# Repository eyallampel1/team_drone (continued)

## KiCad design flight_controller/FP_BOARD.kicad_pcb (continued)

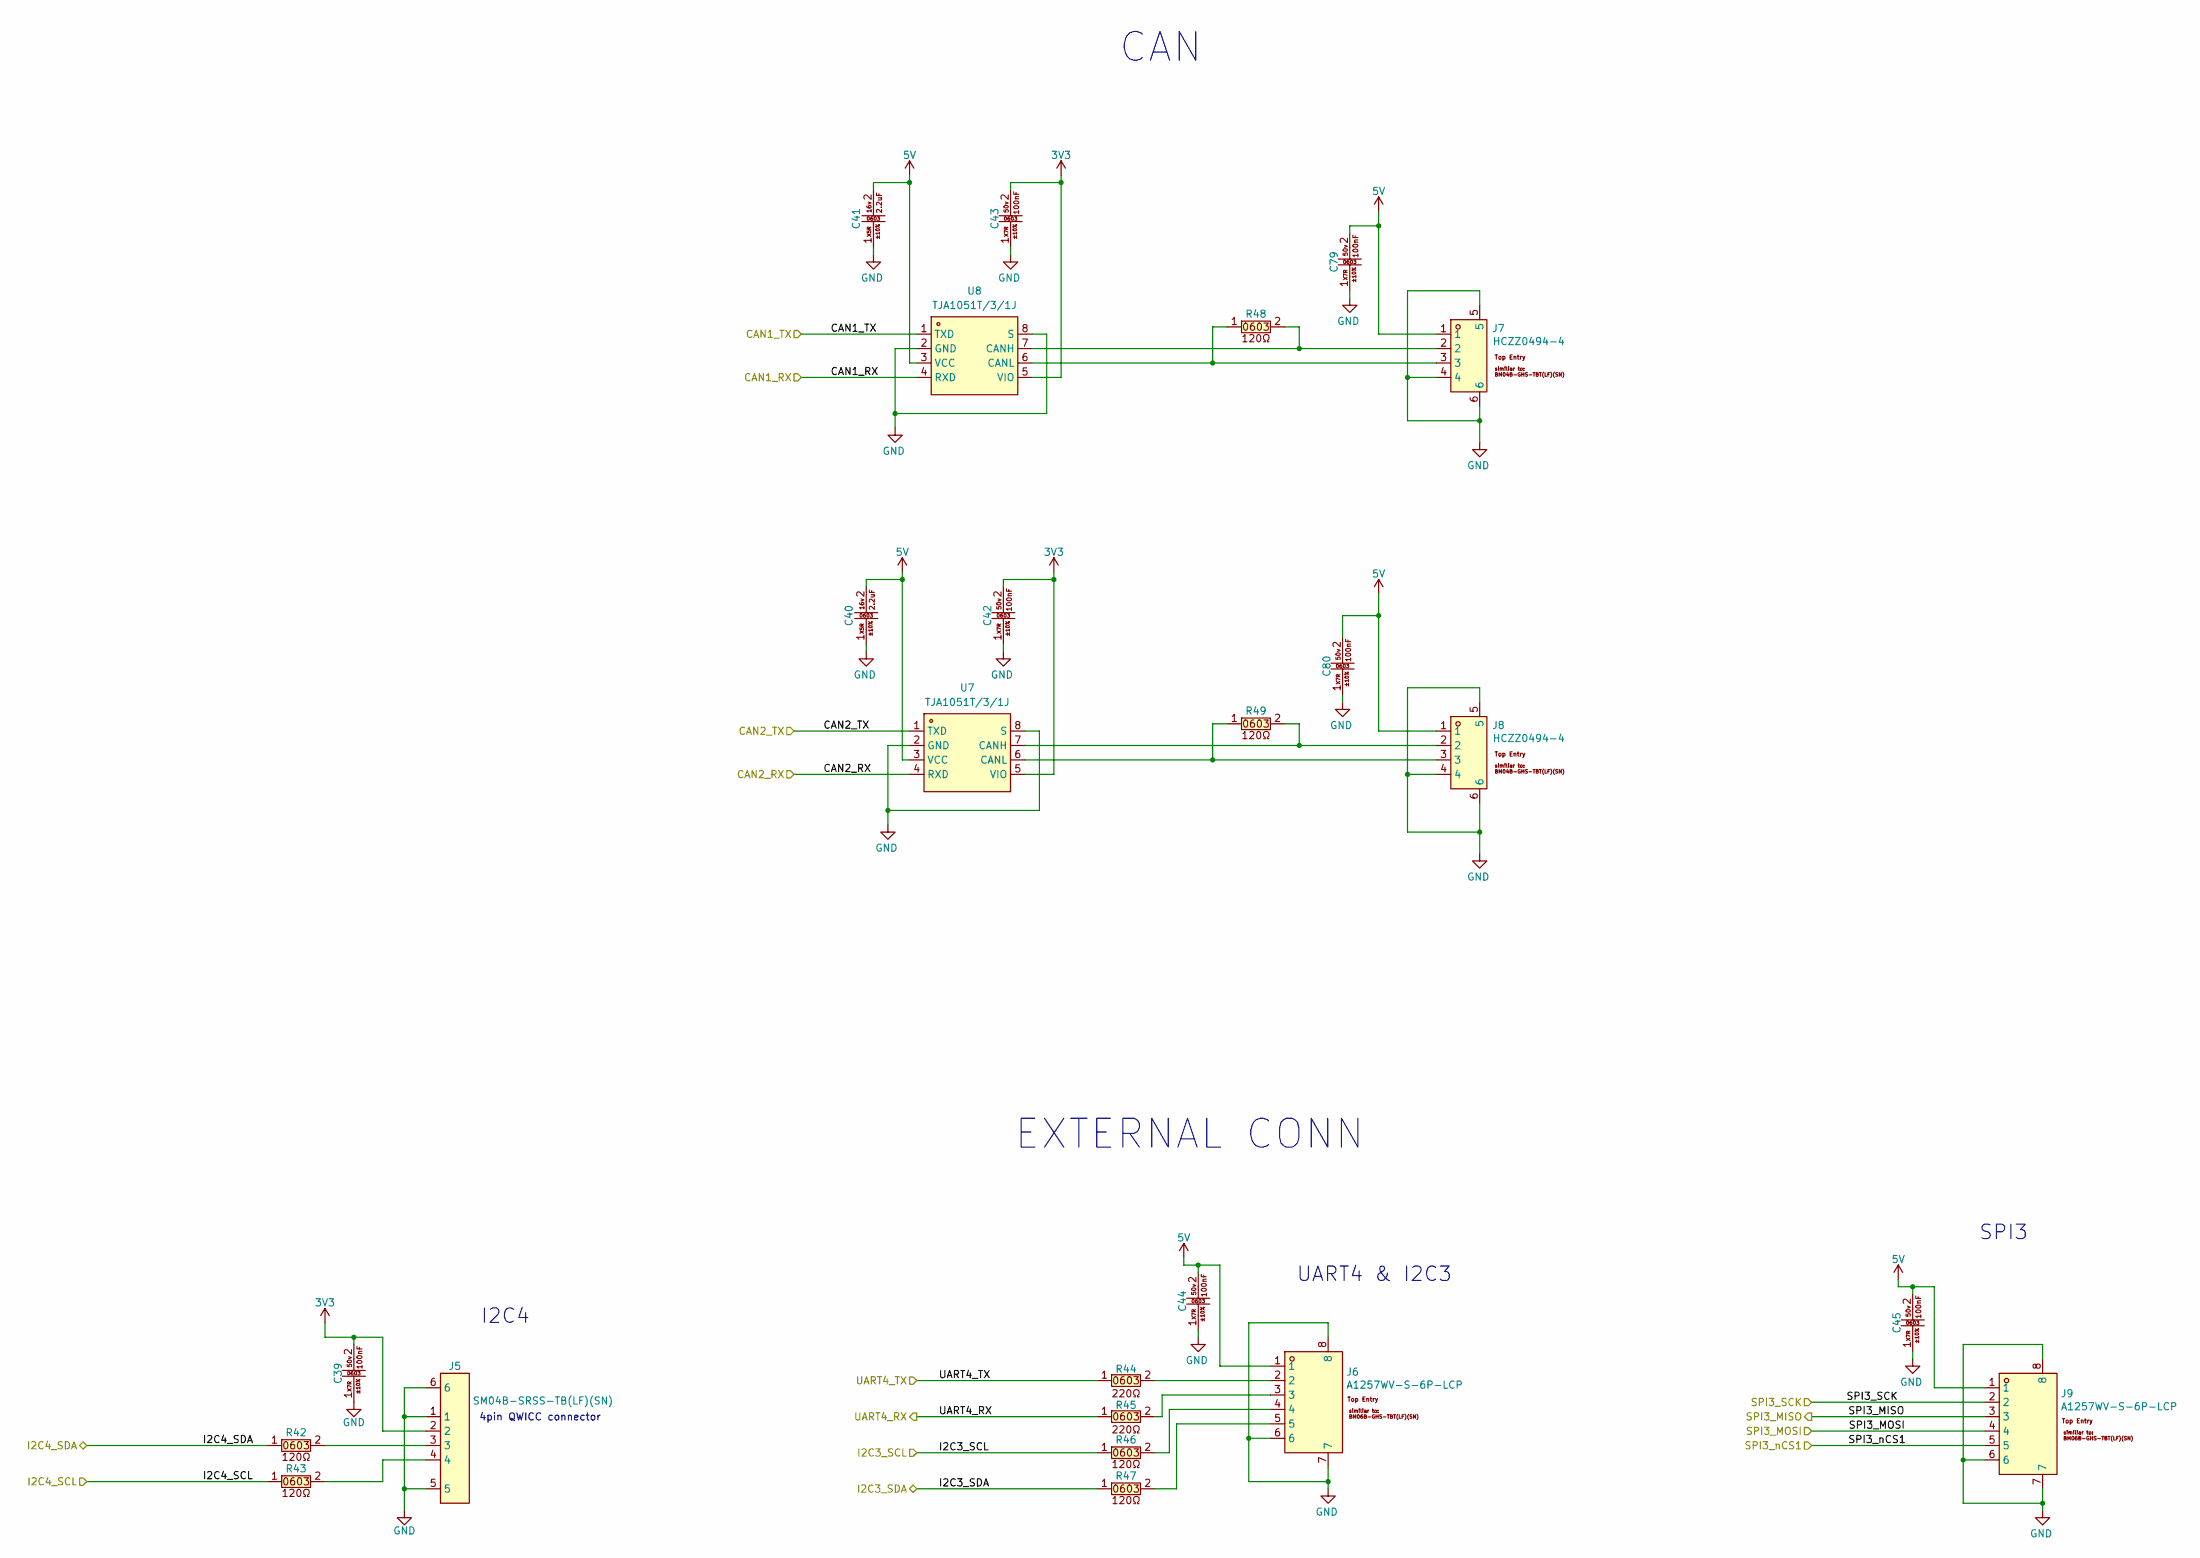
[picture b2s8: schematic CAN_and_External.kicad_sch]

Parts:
C39, C42, C43, C44, C45, C79, C80: CC0603KRX7R9BB104 (100nf , 0603 ,50v ,X7R); C0603; LCSC Part C14663
C40, C41: CL10A225KO8NNNC (2.2uf , 0603,16v,X5R); C0603; LCSC Part C23630
J5: SM04B-SRSS-TB(LF)(SN); CONN-SMD_4P-P1.00_SM04B-SRSS-TB-LF-SN; LCSC Part C160404
J6, J9: A1257WV-S-6P-LCP; CONN-SMD_A1257WV-S-6P; LCSC Part C225122
J7, J8: HCZZ0494-4; CONN-SMD_4P-P1.25_BM04B-GHS-TBT-LF-SN; LCSC Part C7433500
R42, R43, R46, R47, R48, R49: 603WAF1200T5E; R0603; LCSC Part C22787
R44, R45: 0603WAF2200T5E (220ohm , 0603); R0603; LCSC Part C22962
U7, U8: TJA1051T/3/1J; SOIC-8_L4.9-W3.9-P1.27-LS6.0-BL; LCSC Part C38695

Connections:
/FDCAN1_RX: U8.4 (RXD); also elsewhere on the board
/FDCAN1_TX: U8.1 (TXD); also elsewhere on the board
/FDCAN2_RX: U7.4 (RXD); also elsewhere on the board
/FDCAN2_TX: U7.1 (TXD); also elsewhere on the board
/I2C3_SCL: R46.1; also elsewhere on the board
/I2C3_SDA: R47.1; also elsewhere on the board
/I2C4_SCL: R43.1; also elsewhere on the board
/I2C4_SDA: R42.1; also elsewhere on the board
/SPI3_MISO: J9.3; also elsewhere on the board
/SPI3_MOSI: J9.4; also elsewhere on the board
/SPI3_SCK: J9.2; also elsewhere on the board
/SPI3_nCS1: J9.5; also elsewhere on the board
/UART4_RX: R45.1; also elsewhere on the board
/UART4_TX: R44.1; also elsewhere on the board
unnamed: J5.3, R42.2
unnamed: J5.4, R43.2
unnamed: J6.2, R44.2
unnamed: J6.3, R45.2
unnamed: J6.4, R46.2
unnamed: J6.5, R47.2
unnamed: J8.2, R49.2, U7.7 (CANH)
unnamed: J8.3, R49.1, U7.6 (CANL)
unnamed: J7.2, R48.2, U8.7 (CANH)
unnamed: J7.3, R48.1, U8.6 (CANL)

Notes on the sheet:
CAN
UART4 & I2C3
SPI3
4pin QWICC connector
EXTERNAL CONN
I2C4

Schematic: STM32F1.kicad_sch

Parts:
C29, C30: CC0603JRNPO9BN100 (10pF , 0603 ,50V ,X7R); C0603; LCSC Part C106245
C31, C32, C33, C34, C35: CC0603KRX7R9BB104 (100nf , 0603 ,50v ,X7R); C0603; LCSC Part C14663
C36: CL10B105KA8NNNC (1uf ,0603 ,25v ,X7R); C0603; LCSC Part C29936
D3: 0603 Green 509-620mcd; LED0603-RD; LCSC Part C12624
D4: KT-0603R; LED0603-RD; LCSC Part C2286
J21: HB-PH9-12727PB2GOB; HDR-SMD_14P-P1.27-V-M-R2-C7-LS5.5; LCSC Part C6332251
R19, R23, R24: 603WAF1000T5E (100ohm , 0603); R0603; LCSC Part C22775
R20, R21: 0603WAF2200T5E (220ohm , 0603); R0603; LCSC Part C22962
R22, R25: 0603WAF1002T5E (10kohm , 0603); R0603; LCSC Part C25804
SW2: 6.0*6.0*6.0; SW-SMD_4P-L6.0-W6.0-P4.50-LS8.6; LCSC Part C5127964
TP13, TP14, TP15, TP16, TP17: TestPoint; TestPoint_Pad_2.0x2.0mm
U4: STM32F103C8T6; LQFP-48_L7.0-W7.0-P0.50-LS9.0-BL; LCSC Part C8734
X3: X322524MLB4SI_C5210646; CRYSTAL-SMD_4P-L3.2-W2.5-BL; LCSC Part C5210646

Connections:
/IO_CH1: U4.10 (PA0-WKUP); also elsewhere on the board
/IO_CH2: U4.11 (PA1); also elsewhere on the board
/IO_CH3: U4.45 (PB8); also elsewhere on the board
/IO_CH4: U4.46 (PB9); also elsewhere on the board
/IO_CH5: U4.16 (PA6); also elsewhere on the board
/IO_NSAFETY_SWITCH_LED_OUT: U4.26 (PB13); also elsewhere on the board
/IO_PPM_INPUT: U4.29 (PA8); also elsewhere on the board
/IO_RSSI_IN: U4.15 (PA5), U4.33 (PA12); also elsewhere on the board
/IO_SAFETY_SWITCH_IN: U4.41 (PB5); also elsewhere on the board
/IO_SBUS_INPUT: U4.22 (PB11); also elsewhere on the board
/IO_SBUS_OUTPUT: U4.21 (PB10); also elsewhere on the board
/IO_USART1_RX_DSM: J21.13, U4.31 (PA10); also elsewhere on the board
/NSBUS_OUT_EN: U4.40 (PB4); also elsewhere on the board
/STM32F1/FMU_USART6_RX_IO_USART2_TX: R20.2, U4.12 (PA2)
/STM32F1/FMU_USART6_TX_IO_USART2_RX: R21.2, U4.13 (PA3)
/STM32F1/IO_CH6: U4.17 (PA7)
/STM32F1/IO_CH7: U4.18 (PB0)
/STM32F1/IO_CH8: U4.19 (PB1)
/STM32F1/IO_LED1: R23.2, U4.28 (PB15)
/STM32F1/IO_LED2: R24.2, U4.27 (PB14)
/STM32F1/IO_SPARE_GPIO1: TP17.1, U4.42 (PB6)
/STM32F1/IO_SPARE_GPIO2: TP16.1, U4.43 (PB7)
/STM32F1/IO_SWCLK: J21.6, U4.37 (PA14)
/STM32F1/IO_SWDIO: J21.4, U4.34 (PA13)
/STM32F1/IO_SWO: J21.8, U4.39 (PB3)
/STM32F1/IO_USART1_TX_VCP: J21.14, U4.30 (PA9)
/STM32F1/IO_VDD_SERVO_SENS: U4.14 (PA4)
/STM32F1/STM32F1_NRST: SW2.1, SW2.2, U4.7 (NRST)
/STM32F1/USART6_RX_FROM_IO-RC_INPUT: R20.1; also elsewhere on the board
/STM32F1/USART6_TX_TO_IO-NC: R21.1; also elsewhere on the board
unnamed: D3.1 (K), R23.1
unnamed: D4.1 (K), R24.1
unnamed: J21.11, R19.1
unnamed: R25.1, U4.44 (BOOT0)
unnamed: R22.2, U4.20 (PB2)
unnamed: TP13.1, U4.2 (PC13-TAMPER-RTC)
unnamed: TP14.1, U4.3 (PC14-OSC32_IN)
unnamed: TP15.1, U4.4 (PC15-OSC32_OUT)
unnamed: C30.2, U4.5 (PD0-OSC_IN), X3.1
unnamed: C29.2, U4.6 (PD1-OSC_OUT), X3.3

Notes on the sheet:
* PA5 & PA12 SAME NAME - IO_PPM_INPUT TMR1 & ADC12
LEDS
JTAG/SW CONN
Crystal 24MHz
NRST has an internal pullup
Original part number for the stm32 v3 set is : FTSH-107-01-L-DV-K-A

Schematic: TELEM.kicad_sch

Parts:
C60, C61, C62: CC0603KRX7R9BB104 (100nf , 0603 ,50v ,X7R); C0603; LCSC Part C14663
J13, J14, J15: A1257WV-S-6P-LCP; CONN-SMD_A1257WV-S-6P; LCSC Part C225122
R58, R59, R60, R61, R62, R63, R64, R65, R66, R67, R68, R69: 0603WAF2200T5E (220ohm , 0603); R0603; LCSC Part C22962

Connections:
/I2C2_SCL: R58.1; also elsewhere on the board
/UART2_CTS_TELEM3: R65.1; also elsewhere on the board
/UART2_RTS_TELEM3: R66.1; also elsewhere on the board
/UART2_RX_TELEM3: R64.1; also elsewhere on the board
/UART2_TX_TELEM3: R63.1; also elsewhere on the board
/UART5_CTS_TELEM2: R61.1; also elsewhere on the board
/UART5_RTS_TELEM2: R62.1; also elsewhere on the board
/UART5_RX_TELEM2: R60.1; also elsewhere on the board
/UART5_TX_TELEM2: R59.1; also elsewhere on the board
/UART7_CTS_TELEM1: R69.1; also elsewhere on the board
/UART7_RX_TELEM1: R68.1; also elsewhere on the board
/UART7_TX_TELEM1: R67.1; also elsewhere on the board

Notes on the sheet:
TELEM1
TELEM2
TELEM3

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
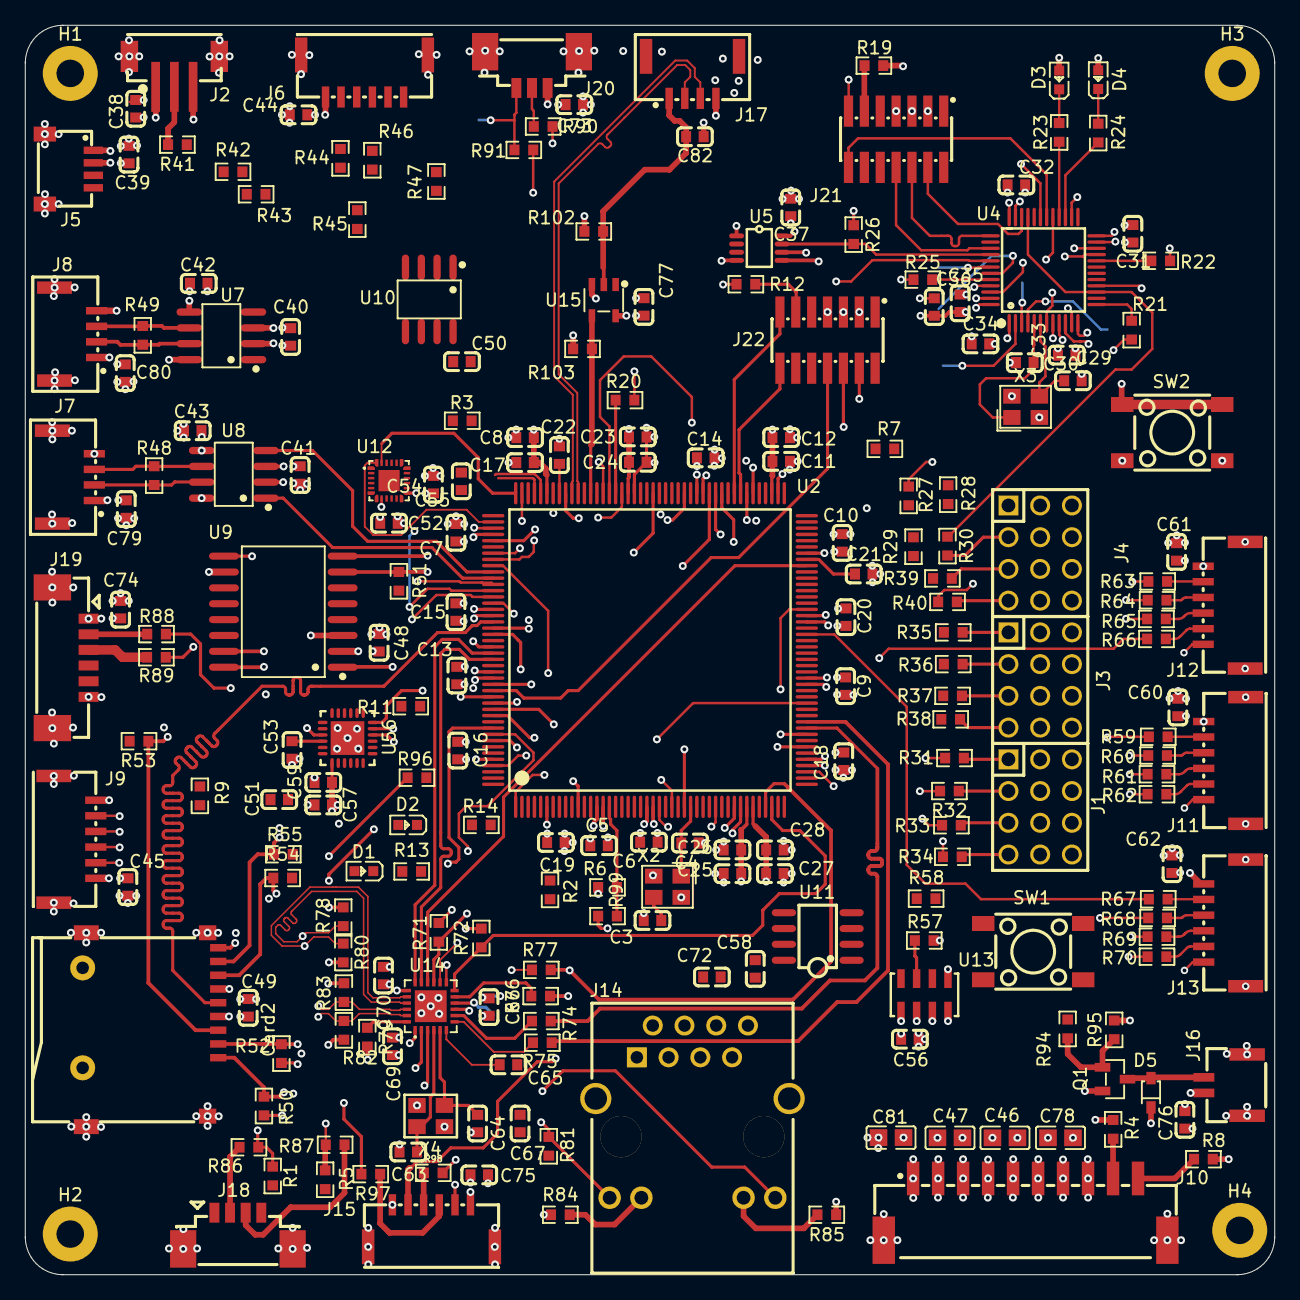
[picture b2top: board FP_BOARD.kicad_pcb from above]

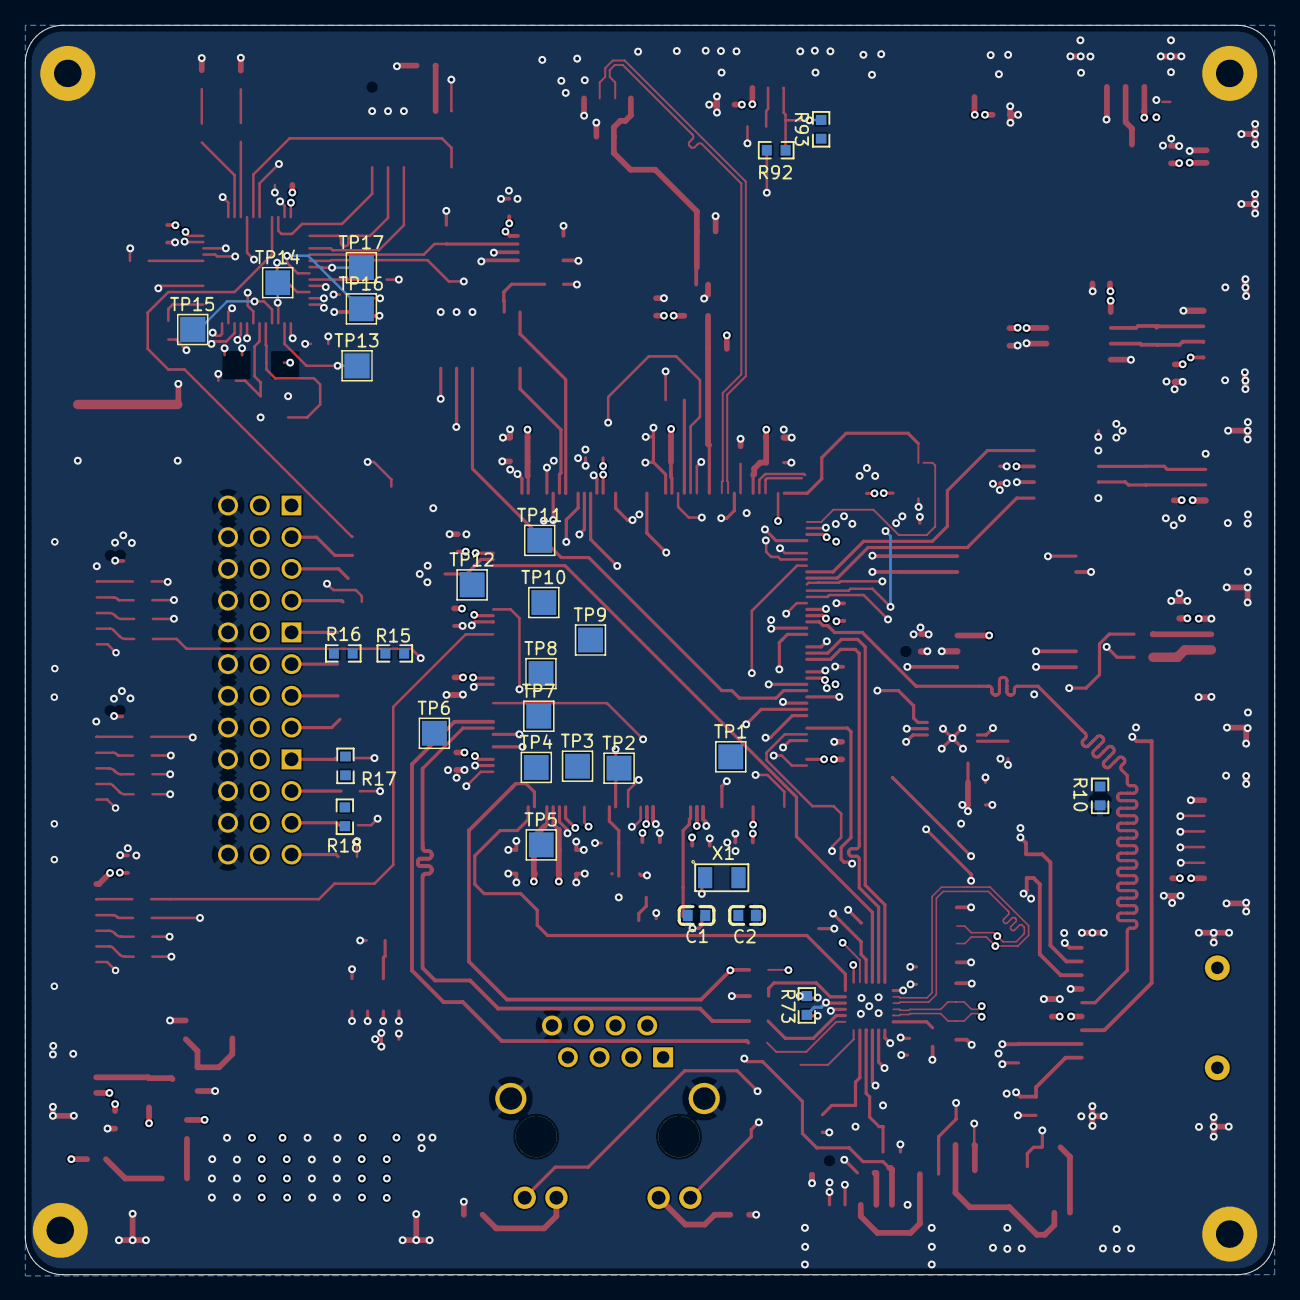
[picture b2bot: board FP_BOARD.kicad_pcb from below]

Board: 6 copper layers, 100.0 x 100.0 mm, 249 parts (28 on the bottom side), 223 nets.

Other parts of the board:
C48, C49, C50, C51, C52, C54, C55, C56, C58, C59: CC0603KRX7R9BB104 (100nf , 0603 ,50v ,X7R); C0603
C53: CC0603KRX7R9BB474 (470nF , 0603 ,50V ,X7R); C0603
C57: CL10A225KO8NNNC (2.2uf , 0603,16v,X5R); C0603
Card2: TF-01A; TF-SMD_TF-01A
J11, J12: A1257WV-S-6P-LCP; CONN-SMD_A1257WV-S-6P
R50, R51, R52, R53, R54, R55, R57: 0603WAF1002T5E; R0603
R70: 0603WAF2200T5E (220ohm , 0603); R0603
U9: W25Q512JVFIQ; SOIC-16_L10.3-W7.5-P1.27-LS10.4-BL
U10: 24LC64-I/SN; SOIC-8_L4.9-W3.9-P1.27-LS6.0-BL
U11: FM25V02A-GTR; SOIC-8_L5.0-W4.0-P1.27-LS6.0-BL
U12: MPU6500; QFN-24_L3.0-W3.0-P0.40-BL-EP
U13: MS561101BA03-50; SENSORS-SMD_MS5611-01BA03
U56: ICM-20689; QFN-24_L4.0-W4.0-P0.50-TL-EP2.6

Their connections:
/I2C2_SCL: U13.8 (SCLK); also elsewhere on the board
/I2C2_SDA: R57.1, U13.7 (SDI/SDA); also elsewhere on the board
/I2C3_SCL: U10.6 (SCL); also elsewhere on the board
/I2C3_SDA: U10.5 (SDA); also elsewhere on the board
/QUADSPI_BK1_IO0: U9.15 (DI(IO0)); also elsewhere on the board
/QUADSPI_BK1_IO1: U9.8 (DO(IO1)); also elsewhere on the board
/QUADSPI_BK1_IO2: U9.9 (WP#(IO2)); also elsewhere on the board
/QUADSPI_BK1_IO3: U9.1 (HOLD#orRESET#(IO3)); also elsewhere on the board
/QUADSPI_BK1_NCS: R51.1, U9.7 (~CS); also elsewhere on the board
/QUADSPI_CLK: U9.16 (CLK); also elsewhere on the board
/SDMMC2_CLK: Card2.5 (CLK(SCLK)); also elsewhere on the board
/SDMMC2_CMD: Card2.3 (CMD(DI)), R53.1; also elsewhere on the board
/SDMMC2_D0: Card2.7 (DAT0(D0)), R54.1; also elsewhere on the board
/SDMMC2_D1: Card2.8 (DAT1(RSV)), R55.1; also elsewhere on the board
/SDMMC2_D2: Card2.1 (DAT2(RSV)), R50.1; also elsewhere on the board
/SDMMC2_D3: Card2.2 (CDDAT3(CS)), R52.1; also elsewhere on the board
/SD_CARD_DETECT: Card2.9 (CD); also elsewhere on the board
/SPI1_DRDY1: U56.12 (INT); also elsewhere on the board
/SPI1_MISO: U56.9 (AD0/SDO); also elsewhere on the board
/SPI1_MOSI: U56.24 (SDA/SDI); also elsewhere on the board
/SPI1_SCK: U56.23 (SCL/SCLK); also elsewhere on the board
/SPI1_nCS1: U56.22 (nCS); also elsewhere on the board
/SPI2_DRDY2_INT2: U12.12 (INT); also elsewhere on the board
/SPI2_MISO: U12.9 (SDO/AD0); also elsewhere on the board
/SPI2_MOSI: U12.24 (SDA/SDI); also elsewhere on the board
/SPI2_SCK: U12.23 (SCL/SCLK); also elsewhere on the board
/SPI2_nCS1: U12.22 (nCS); also elsewhere on the board
/SPI5_MISO: U11.2 (SO); also elsewhere on the board
/SPI5_MOSI: U11.5 (SI); also elsewhere on the board
/SPI5_SCK: U11.6 (SCK); also elsewhere on the board
/SPI5_nCS1: U11.1 (/CS); also elsewhere on the board
/UART7_RTS_TELEM1: R70.1; also elsewhere on the board
unnamed: C55.2, U12.10 (REGOUT)
unnamed: C53.2, U56.10 (REGOUT)

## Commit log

2026-01-22 initial commit from local
2026-01-22 Update Scheme
2026-01-22 Update Scheme & DEV_DOC
2026-01-25 updating symbols as in the shared library
2026-01-29 update debug conn
2026-01-29 Update Block Diagram
2026-01-31 Uploading a guide to working with a easteda2kicad
2026-02-01 gps and power blocks
2026-02-05 ALL CONNECTORS, ETH, SERVO,RC,SPI,FLASH and more. to finish GPSand STM32 PINOUT
2026-02-10 cleanup and improvements
2026-02-12 Schematic complete, ready for layout. Added USB, TPs, power conn, updated clocks, ran Rules Checker and general review
2026-02-14 Started the placement process
2026-02-14 Placment in progress
2026-02-14 Almost done with placement , fixed some 3d models , fixed r56 to u56
2026-02-15 Finished placement
2026-02-15 moved all to components to top
2026-02-16 Updated power and usb connectors, annotations and netlist check
2026-02-19 Update Scheme 19/02/26
2026-02-20 Replace power connector
2026-02-20 Fixed 10pin and pushed to pcb
2026-02-20 Revert to state of commit 2458262 moved all to components to top
    Reverts commits: d012532, 3d9c600, 58bc0ac
2026-02-20 renamed some connectors to j instead of cn
2026-02-21 Advanced in routing
2026-02-22 Advanced in routing more
2026-02-22 Advanced in the routing of decup cap
2026-02-22 Started critical lines routing
2026-02-22 Trying to route ethernet
2026-02-23 Changed eth net name and started diff route , added custom rules file for diff
2026-02-25 Added some eth lines
2026-02-26 Added stuff
2026-02-27 Routed all match length buses
2026-03-02 Router a bit more
2026-03-04 Almost finish with initial routing
2026-03-05 Finished routing
2026-03-05 Finished all DRC
2026-03-05 Finished Board and silkscreen
2026-03-07 routing in progress for PDB
2026-03-07 Finished routing of PDB
2026-03-07 Finished PDB
